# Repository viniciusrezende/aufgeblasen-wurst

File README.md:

# aufgeblasen-wurst
Schematics, board layout and part list for a fuzz stompbox/pedal.

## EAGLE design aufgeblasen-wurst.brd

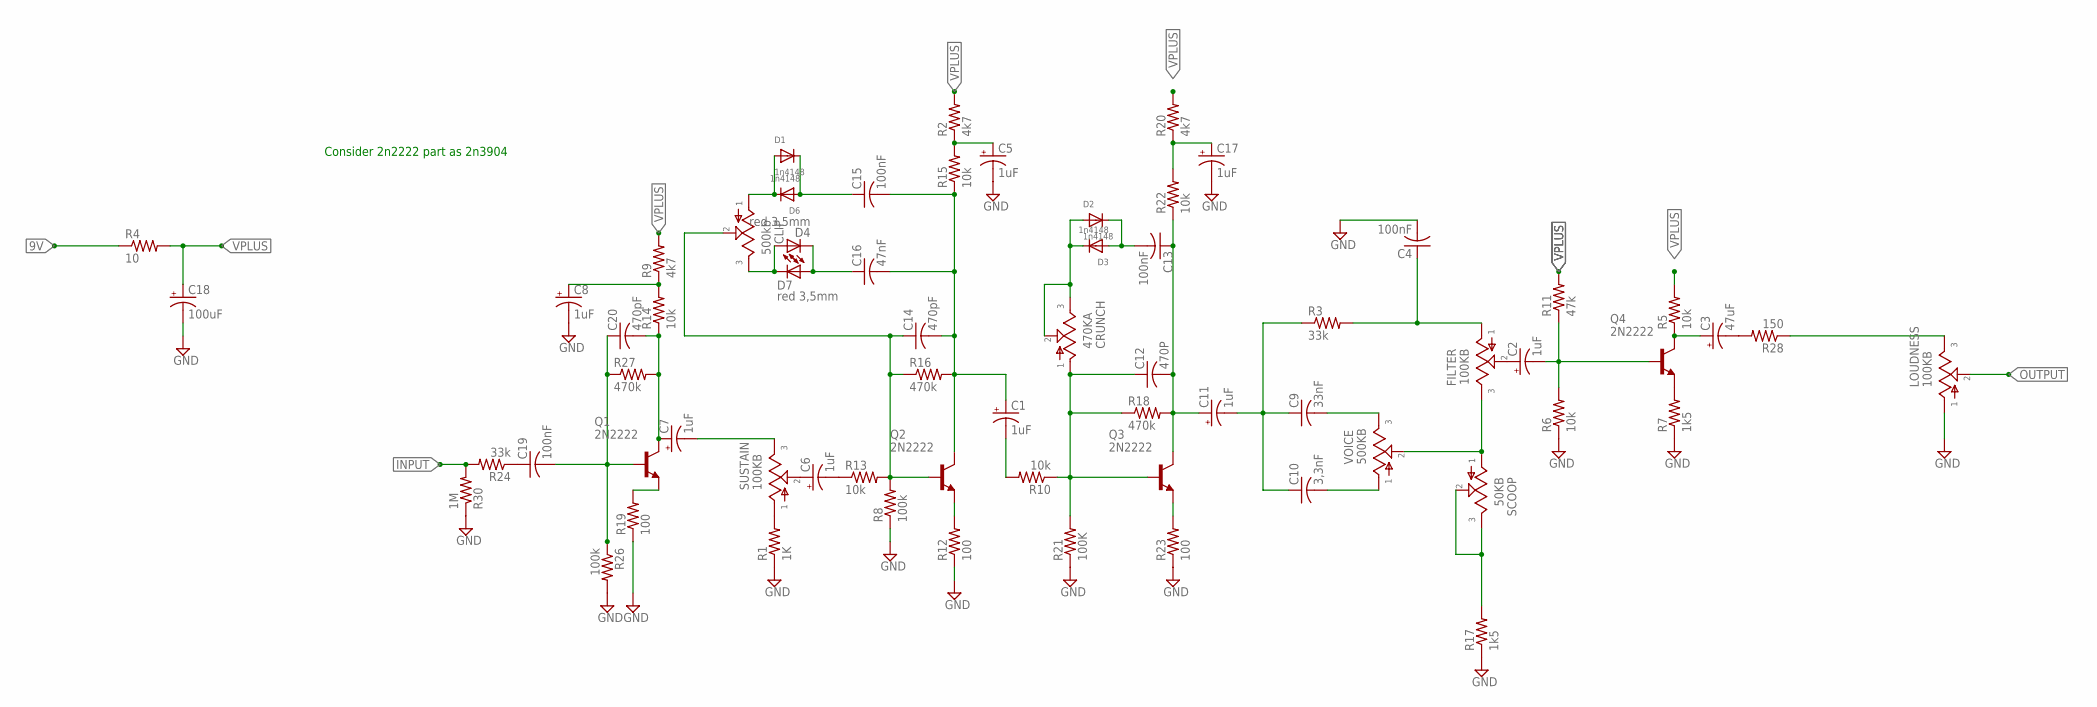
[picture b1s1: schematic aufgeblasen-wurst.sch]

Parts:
C1, C2, C5, C6, C7, C8, C11, C17: 1uF; TT2D5
C3: 47uF; TT2D5
C4, C13, C15, C19: 100nF; C050-025X075
C9: 33nF; C050-025X075
C10: 3,3nF; C050-025X075
C12: 470P; C050-025X075
C14, C20: 470pF; C050-025X075
C16: 47nF; C050-025X075
C18: 100uF; TT2D5
CLIP: 500kb; POT
CRUNCH: 470KA; POT
D1, D2, D3, D6: 1n4148; DO-1N4148
D4, D7: red 3,5mm; LED3MM
FILTER: 100KB; POT
LOUDNESS: 100KB; POT
Q1, Q2, Q3, Q4: 2N2222; TO92-EBC-OVAL
R1: 1K; 0207/7
R2, R9, R20: 4k7; 0207/7
R3, R24: 33k; 0207/7
R4: 10; 0207/7
R5, R6, R10, R13, R14, R15, R22: 10k; 0207/7
R7, R17: 1k5; 0207/7
R8, R26: 100k; 0207/7
R11: 47k; 0207/7
R12, R19, R23: 100; 0207/7
R16, R18, R27: 470k; 0207/7
R21: 100K; 0207/7
R28: 150; 0207/7
R30: 1M; 0207/7
SCOOP: 50KB; POT
SUSTAIN: 100KB; POT
VOICE: 500KB; POT

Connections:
9V: R4.1
GND: C4.2, C5.-, C8.-, C17.-, C18.-, LOUDNESS.1, R1.1, R6.1, R7.1, R8.1, R12.1, R17.1, R19.1, R21.1, R23.1, R26.2, R30.1
INPUT: R24.2, R30.2
JUMP1: LOUDNESS.3, R28.1
JUMP3: C14.1, CLIP.2, Q2.B, R8.2, R13.2, R16.1
unnamed: C19.2, C20.1, Q1.B, R26.1, R27.1
unnamed: C19.1, R24.1
unnamed: Q1.E, R19.2
unnamed: C6.+, SUSTAIN.2
unnamed: C7.-, SUSTAIN.3
unnamed: R1.2, SUSTAIN.1
unnamed: C2.+, FILTER.2
unnamed: C6.-, R13.1
unnamed: Q2.E, R12.2
unnamed: C1.+, C14.2, C15.2, C16.2, Q2.C, R15.1, R16.2
unnamed: CLIP.3, D4.A, D7.K (C)
unnamed: C8.+, R9.1, R14.2
unnamed: C16.1, D4.K (C), D7.A
unnamed: C15.1, D1.C, D6.A
unnamed: CLIP.1, D1.A, D6.C
unnamed: C5.+, R2.1, R15.2
unnamed: C1.-, R10.2
unnamed: C11.+, C12.2, C13.1, Q3.C, R18.2, R22.1
unnamed: C12.1, CRUNCH.1, Q3.B, R10.1, R18.1, R21.2
unnamed: Q3.E, R23.2
unnamed: CRUNCH.2, CRUNCH.3, D2.A, D3.C
unnamed: C13.2, D2.C, D3.A
unnamed: C17.+, R20.1, R22.2
unnamed: C9.1, C10.1, C11.-, R3.1
unnamed: C10.2, VOICE.1
unnamed: C4.1, FILTER.1, R3.2
unnamed: C9.2, VOICE.3
unnamed: FILTER.3, SCOOP.1, VOICE.2
unnamed: R17.2, SCOOP.2, SCOOP.3
unnamed: C2.-, Q4.B, R6.2, R11.1
unnamed: C3.+, Q4.C, R5.1
unnamed: Q4.E, R7.2
unnamed: C7.+, C20.2, Q1.C, R14.1, R27.2
unnamed: C3.-, R28.2
OUTPUT: LOUDNESS.2
VPLUS: C18.+, R2.2, R4.2, R5.2, R9.2, R11.2, R20.2

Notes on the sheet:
Consider 2n2222 part as 2n3904

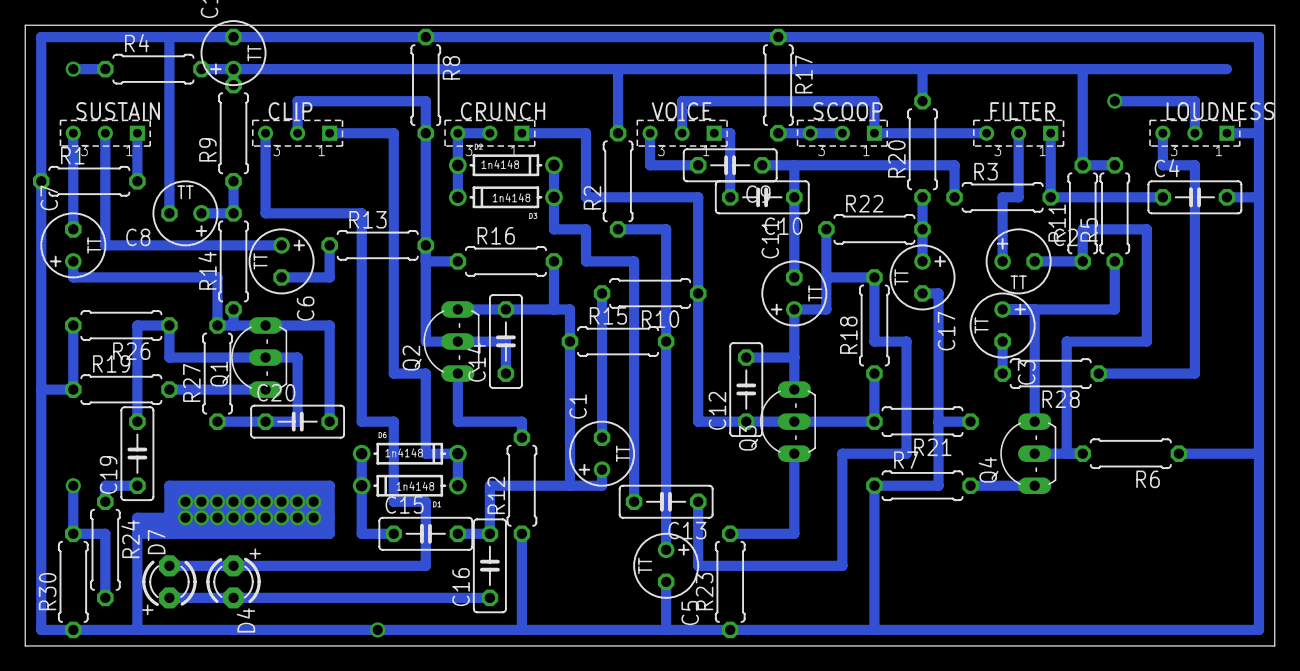
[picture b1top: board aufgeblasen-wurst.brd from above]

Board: 2 copper layers, 99.0 x 49.2 mm, 65 parts (0 on the bottom side), 39 nets.

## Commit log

2017-02-08 Added: Eagle board and schematic files. Ready to trans pcb. Partlist. Board and Schematic.
